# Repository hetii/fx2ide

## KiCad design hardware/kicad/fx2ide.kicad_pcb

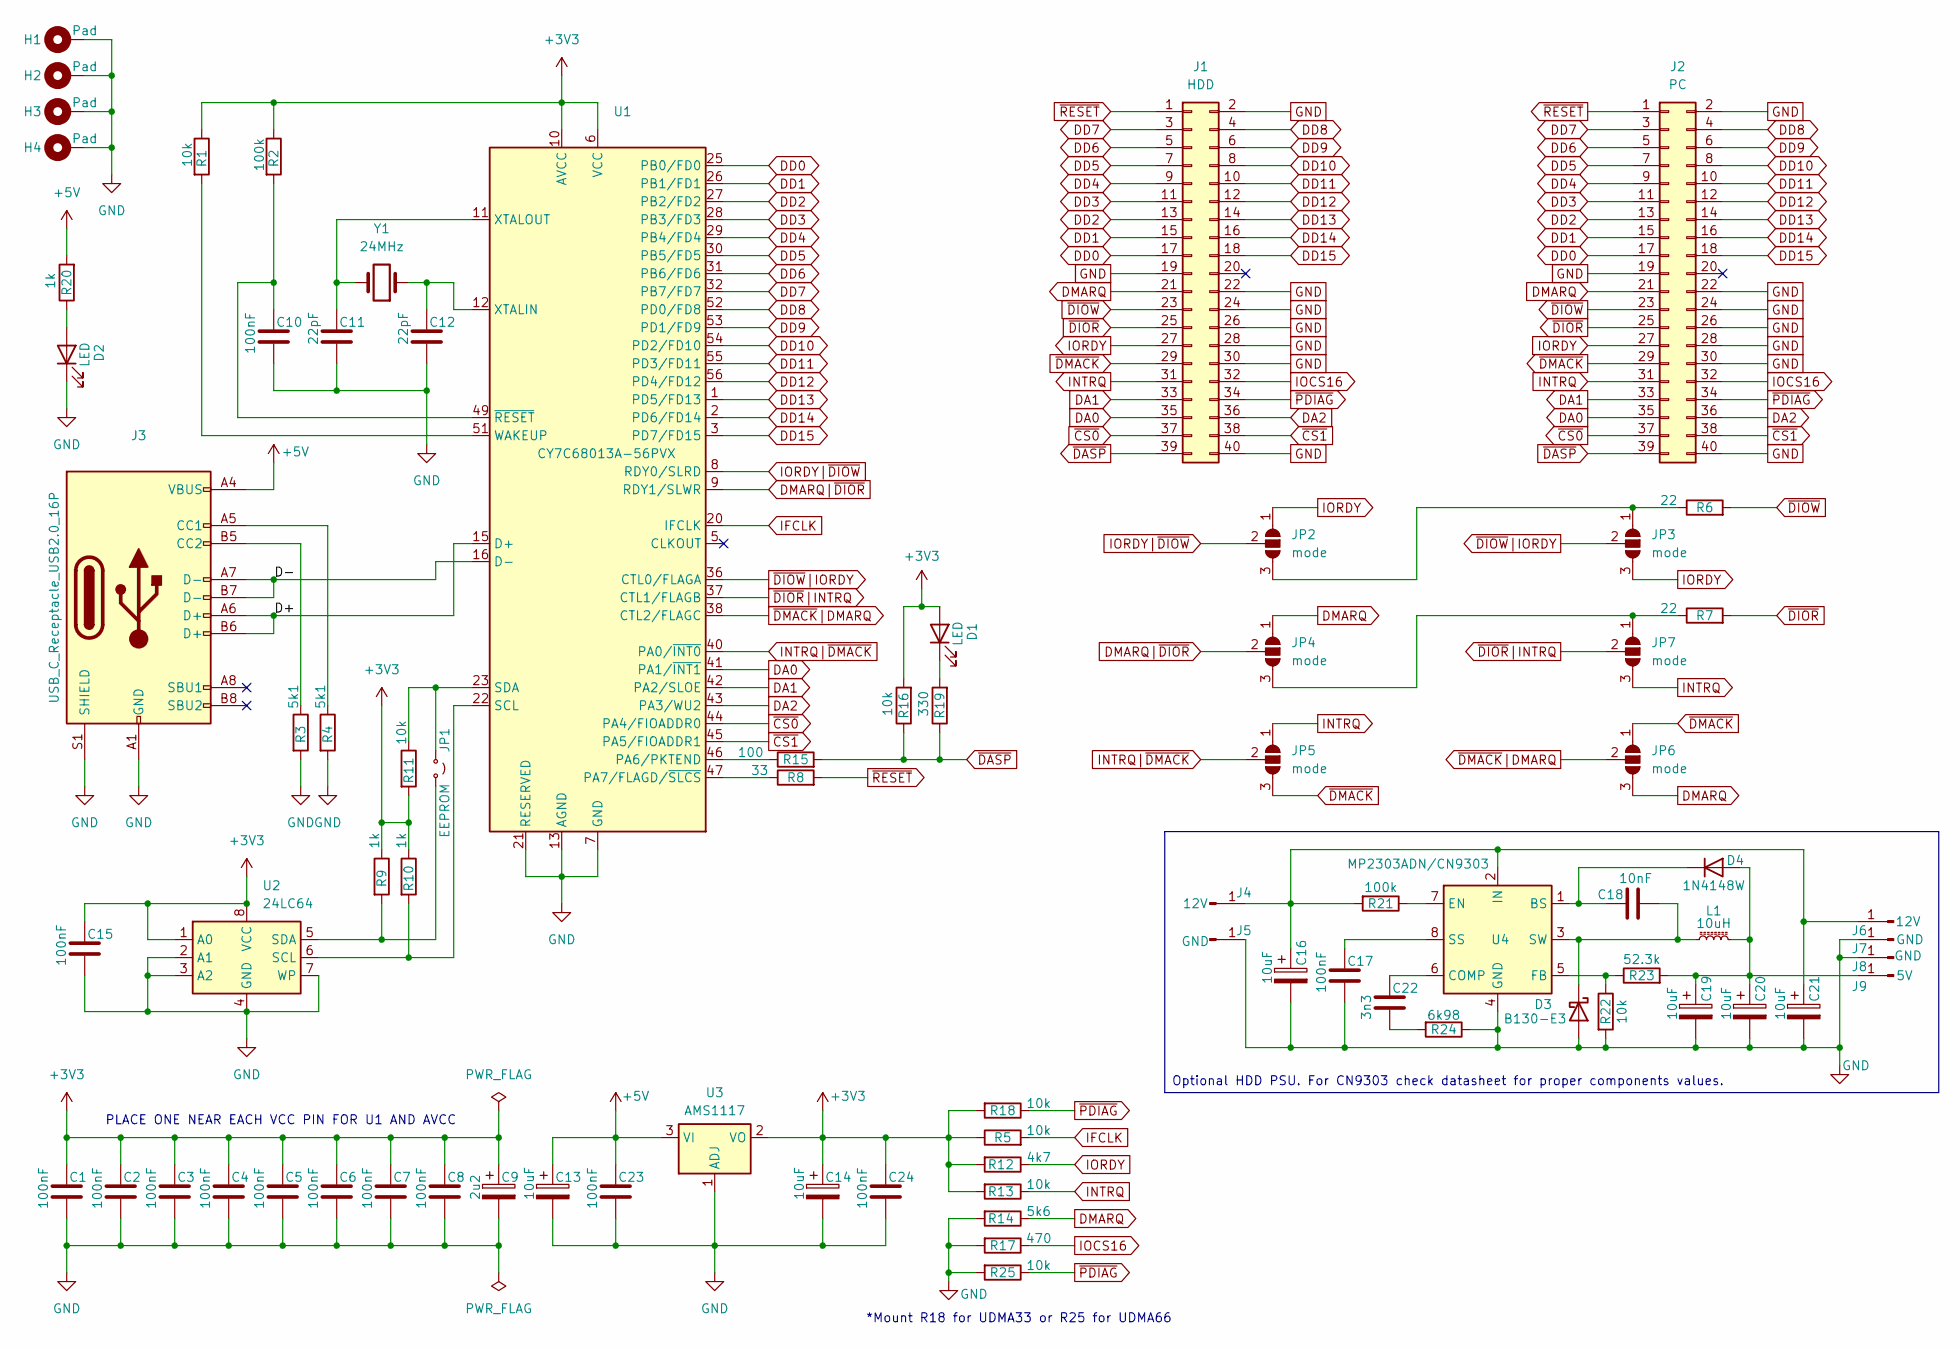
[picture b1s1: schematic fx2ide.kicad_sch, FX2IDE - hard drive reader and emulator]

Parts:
C1, C2, C3, C4, C5, C6, C7, C8, C10, C15, C17, C23, C24: 100nF; C_0603_1608Metric
C9: 2u2; CP_EIA-3216-12_Kemet-S_HandSolder
C11, C12: 22pF; C_0603_1608Metric
C13, C14, C16, C19, C20, C21: 10uF; CP_EIA-3216-12_Kemet-S_HandSolder
C18: 10nF; C_0603_1608Metric
C22: 3n3; C_0603_1608Metric
D1, D2: LED; D_0603_1608Metric
D3: B130-E3; D_SMA
D4: 1N4148W; D_SOD-123
H1, H2, H3, H4: Pad; MountingHole_3.2mm_M3_Pad_Via
J1: HDD; PinSocket_2x20_P2.54mm_EdgePCB_SMD
J2: PC; IDC-Header_2x20_P2.54mm_Vertical
J3: USB_C_Receptacle_USB2.0_16P; USB_C_Receptacle_GCT_USB4105-xx-A_16P_TopMnt_Horizontal
J4, J6: 12V; SolderWirePad_1x01_SMD_2x4mm
J5, J7, J8: GND; SolderWirePad_1x01_SMD_2x4mm
J9: 5V; SolderWirePad_1x01_SMD_2x4mm
JP1: EEPROM; PinHeader_2x01_P2.54mm_Vertical
JP2, JP3, JP4, JP5, JP6, JP7: mode; SolderJumper-3_P1.3mm_Open_RoundedPad1.0x1.5mm
L1: 10uH; L_AVX_LMLP07A7
R1, R5, R11, R13, R16, R18, R22, R25: 10k; R_0603_1608Metric
R2, R21: 100k; R_0603_1608Metric
R3, R4: 5k1; R_0603_1608Metric
R6, R7: 22; R_0603_1608Metric
R8: 33; R_0603_1608Metric
R9, R10, R20: 1k; R_0603_1608Metric
R12: 4k7; R_0603_1608Metric
R14: 5k6; R_0603_1608Metric
R15: 100; R_0603_1608Metric
R17: 470; R_0603_1608Metric
R19: 330; R_0603_1608Metric
R23: 52.3k; R_0603_1608Metric
R24: 6k98; R_0603_1608Metric
U1: CY7C68013A-56PVX; SSOP-56_7.5x18.5mm_P0.635mm
U2: 24LC64; SOIC-8_3.9x4.9mm_P1.27mm
U3: AMS1117; SOT-223-3_TabPin2
U4: MP2303ADN/CN9303; SOIC-8-1EP_3.9x4.9mm_P1.27mm_EP2.62x3.51mm
Y1: 24MHz; Crystal_HC49-4H_Vertical

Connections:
+3V3: C1.1, C2.1, C3.1, C4.1, C5.1, C6.1, C7.1, C8.1, C9.1, C14.1, C15.1, C24.1, D1.2 (A), R1.1, R2.1, R5.1, R9.1, R10.1, R11.2, R12.2, R13.2, R16.2, R18.2, U1.6 (VCC), U1.10 (AVCC), U1.14 (AVCC), U1.18 (VCC), U1.24 (VCC), U1.34 (VCC), U1.39 (VCC), U1.50 (VCC), U2.1 (A0), U2.8 (VCC), U3.2 (VO)
+5V: C13.1, C23.1, J3.A4 (VBUS), J3.A9 (VBUS), J3.B4 (VBUS), J3.B9 (VBUS), R20.2, U3.3 (VI)
/D+: J3.A6 (D+), J3.B6 (D+), U1.15 (D+)
/D-: J3.A7 (D-), J3.B7 (D-), U1.16 (D-)
DA0: J1.35, J2.35, U1.41 (PA1/~INT1)
DA1: J1.33, J2.33, U1.42 (PA2/SLOE)
DA2: J1.36, J2.36, U1.43 (PA3/WU2)
DD0: J1.17, J2.17, U1.25 (PB0/FD0)
DD1: J1.15, J2.15, U1.26 (PB1/FD1)
DD2: J1.13, J2.13, U1.27 (PB2/FD2)
DD3: J1.11, J2.11, U1.28 (PB3/FD3)
DD4: J1.9, J2.9, U1.29 (PB4/FD4)
DD5: J1.7, J2.7, U1.30 (PB5/FD5)
DD6: J1.5, J2.5, U1.31 (PB6/FD6)
DD7: J1.3, J2.3, U1.32 (PB7/FD7)
DD8: J1.4, J2.4, U1.52 (PD0/FD8)
DD9: J1.6, J2.6, U1.53 (PD1/FD9)
DD10: J1.8, J2.8, U1.54 (PD2/FD10)
DD11: J1.10, J2.10, U1.55 (PD3/FD11)
DD12: J1.12, J2.12, U1.56 (PD4/FD12)
DD13: J1.14, J2.14, U1.1 (PD5/FD13)
DD14: J1.16, J2.16, U1.2 (PD6/FD14)
DD15: J1.18, J2.18, U1.3 (PD7/FD15)
DMARQ: J1.21, J2.21, JP4.1 (A), JP6.3 (B), R14.1
DMARQ|~DIOR: JP4.2 (C), U1.9 (RDY1/SLWR)
GND: C1.2, C2.2, C3.2, C4.2, C5.2, C6.2, C7.2, C8.2, C9.2, C10.2, C11.2, C12.2, C13.2, C14.2, C15.2, C16.2, C17.2, C19.2, C20.2, C21.2, C23.2, C24.2, D2.1 (K), D3.2 (A), H1.1 (1_1), H2.1 (1_1), H3.1 (1_1), H4.1 (1_1), J1.2, J1.19, J1.22, J1.24, J1.26, J1.28, J1.30, J1.40, J2.2, J2.19, J2.22, J2.24, J2.26, J2.28, J2.30, J2.40, J3.A1 (GND), J3.A12 (GND), J3.B1 (GND), J3.B12 (GND), J3.S1 (SHIELD), J5.1 (Pin_1_1), J7.1 (Pin_1_1), J8.1 (Pin_1_1), R3.2, R4.2, R14.2, R17.2, R22.2, R24.1, R25.2, U1.4 (GND), U1.7 (GND), U1.13 (AGND), U1.17 (AGND), U1.19 (GND), U1.21 (RESERVED), U1.33 (GND), U1.35 (GND), U1.48 (GND), U2.2 (A1), U2.3 (A2), U2.4 (GND), U2.7 (WP), U3.1 (ADJ), U4.4 (GND)
IFCLK: R5.2, U1.20 (IFCLK)
INTRQ: J1.31, J2.31, JP5.1 (A), JP7.3 (B), R13.1
INTRQ|~DMACK: JP5.2 (C), U1.40 (PA0/~INT0)
IOCS16: J1.32, J2.32, R17.1
IORDY: J1.27, J2.27, JP2.1 (A), JP3.3 (B), R12.1
IORDY|~DIOW: JP2.2 (C), U1.8 (RDY0/SLRD)
unnamed: C22.2, R24.2
unnamed: D1.1 (K), R19.2
unnamed: D2.2 (A), R20.1
unnamed: C18.1, D3.1 (K), L1.1, U4.3 (SW)
unnamed: C19.1, C20.1, D4.2 (A), J9.1 (Pin_1_1), L1.2, R23.2
unnamed: C18.2, D4.1 (K), U4.1 (BS)
unnamed: J3.A5 (CC1), R4.1
unnamed: J3.B5 (CC2), R3.1
unnamed: C16.1, C21.1, J4.1 (Pin_1_1), J6.1 (Pin_1_1), R21.2, U4.2 (IN)
unnamed: JP1.1 (A), R11.1, U1.23 (SDA)
unnamed: JP1.2 (B), R9.2, U2.5 (SDA)
unnamed: JP2.3 (B), JP3.1 (A), R6.1
unnamed: JP4.3 (B), JP7.1 (A), R7.1
unnamed: R15.1, U1.46 (PA6/PKTEND)
unnamed: R8.1, U1.47 (PA7/FLAGD/~SLCS)
unnamed: R10.2, U1.22 (SCL), U2.6 (SCL)
unnamed: R1.2, U1.51 (WAKEUP)
unnamed: C12.1, U1.12 (XTALIN), Y1.1
unnamed: C11.1, U1.11 (XTALOUT), Y1.2
unnamed: C10.1, R2.2, U1.49 (~RESET)
unnamed: C22.1, U4.6 (COMP)
unnamed: R21.1, U4.7 (EN)
unnamed: R22.1, R23.1, U4.5 (FB)
unnamed: C17.1, U4.8 (SS)
~CS0: J1.37, J2.37, U1.44 (PA4/FIOADDR0)
~CS1: J1.38, J2.38, U1.45 (PA5/FIOADDR1)
~DASP: J1.39, J2.39, R15.2, R16.1, R19.1
~DIOR: J1.25, J2.25, R7.2
~DIOR|INTRQ: JP7.2 (C), U1.37 (CTL1/FLAGB)
~DIOW: J1.23, J2.23, R6.2
~DIOW|IORDY: JP3.2 (C), U1.36 (CTL0/FLAGA)
~DMACK: J1.29, J2.29, JP5.3 (B), JP6.1 (A)
~DMACK|DMARQ: JP6.2 (C), U1.38 (CTL2/FLAGC)
~PDIAG: J1.34, J2.34, R18.1, R25.1
~RESET: J1.1, J2.1, R8.2

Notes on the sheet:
PLACE ONE NEAR EACH VCC PIN FOR U1 AND AVCC
*Mount R18 for UDMA33 or R25 for UDMA66
Optional HDD PSU. For CN9303 check datasheet for proper components values.

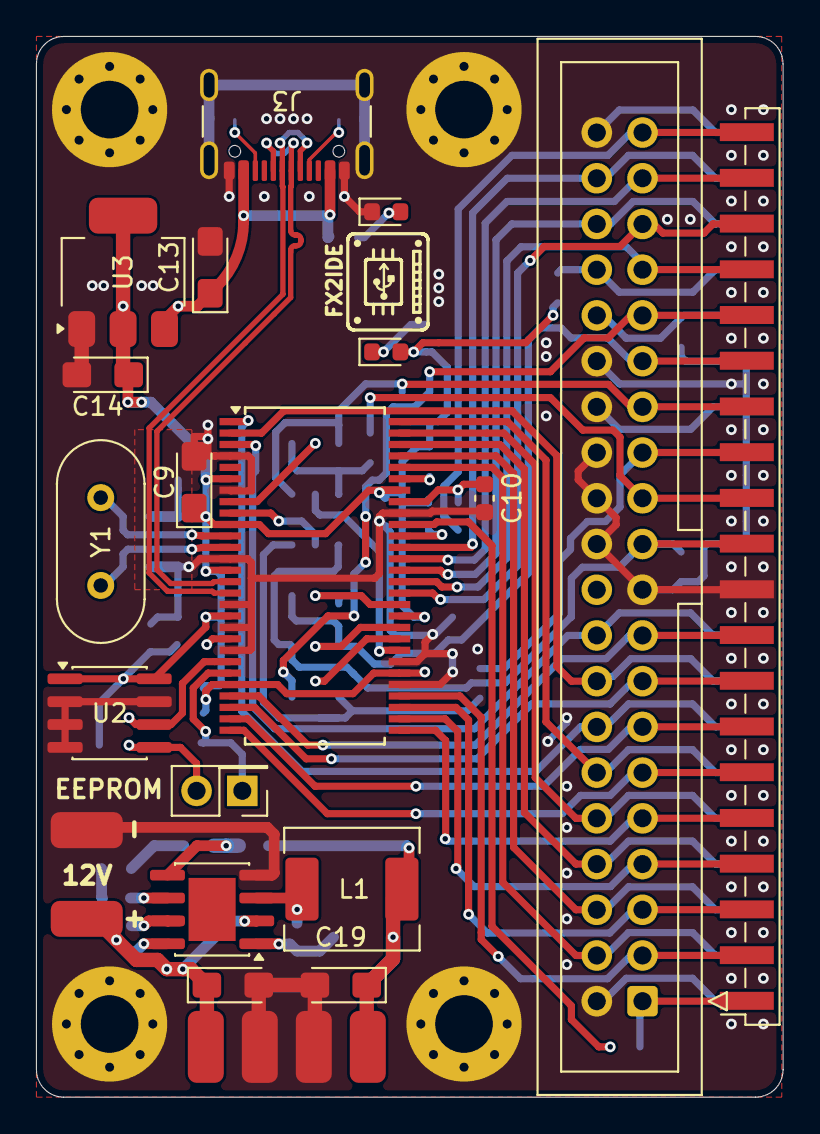
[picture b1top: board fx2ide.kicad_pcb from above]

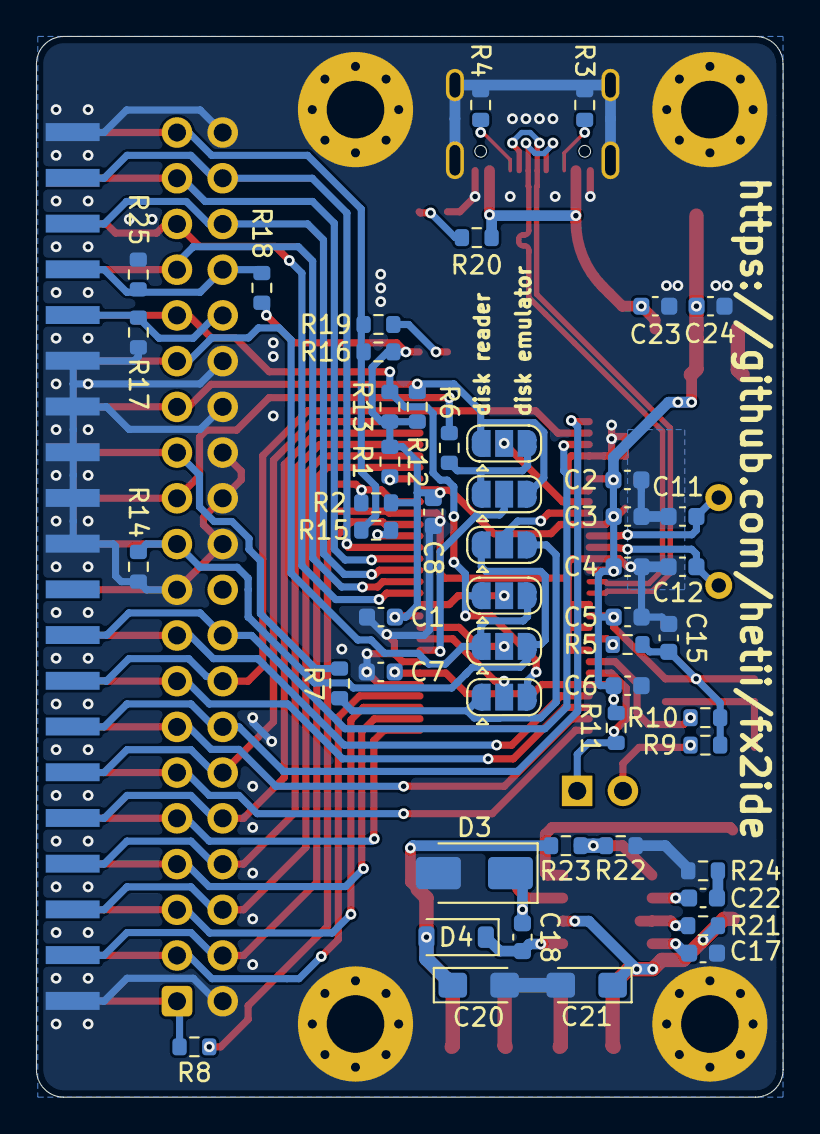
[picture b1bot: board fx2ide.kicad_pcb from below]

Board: 2 copper layers, 41.5 x 58.9 mm, 79 parts (51 on the bottom side), 67 nets.

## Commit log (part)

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2026-06-28 Add kicad project.
